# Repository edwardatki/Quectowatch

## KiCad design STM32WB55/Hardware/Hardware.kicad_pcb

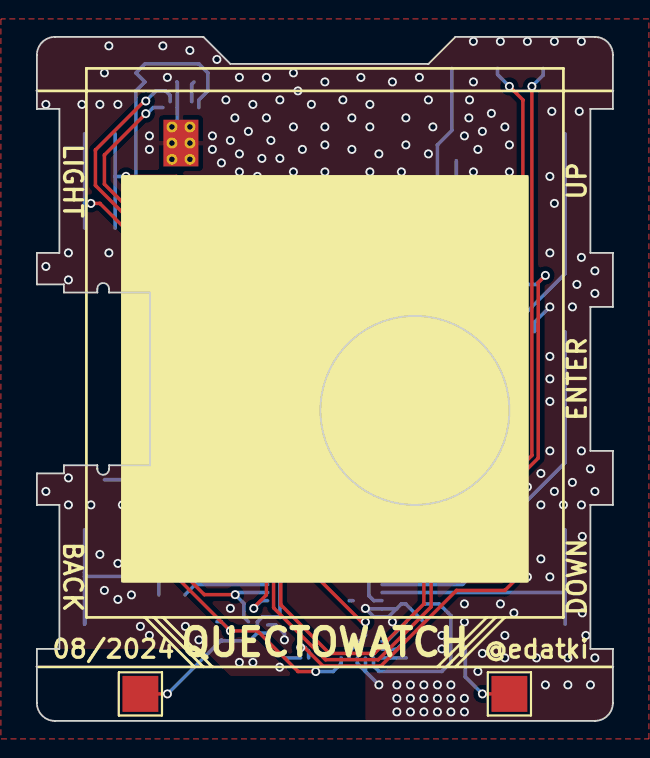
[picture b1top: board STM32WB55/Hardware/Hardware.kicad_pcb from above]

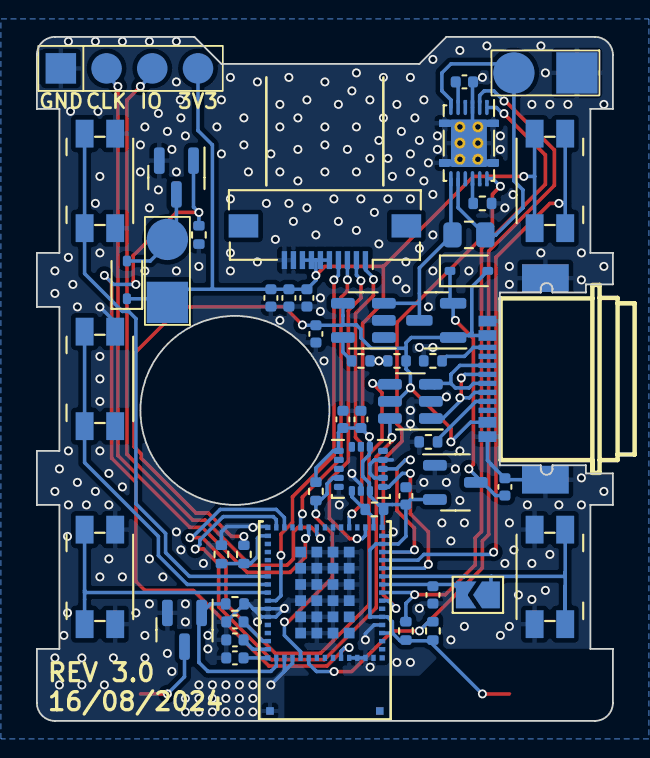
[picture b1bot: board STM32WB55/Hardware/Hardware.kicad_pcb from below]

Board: 2 copper layers, 32.0 x 38.0 mm, 51 parts (49 on the bottom side), 42 nets.

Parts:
C1, C7, C11: 100nF; C_0402_1005Metric
C2, C3, C4: 3.3pF; C_0402_1005Metric
C5: 470nF; C_0402_1005Metric
C6, C8, C9, C10, C13: 1uF; C_0402_1005Metric
C12: 10uF; C_0402_1005Metric
D1, D4: 1N5819WS; D_SOD-323
J1: USB_C_Receptacle_USB2.0; USB-C-SMD_SHOUHAN_TYPE-C-16PFS-2JCB1.2-H6.5
J2: PROG; 1x04_2.54_Pads
J3: BAT; 1x02_2.54_Pads
J4: LCD; Molex_54548-1071_1x10-1MP_P0.5mm_Horizontal
J5: AUX; 1x02_2.54_Pads
J6: LED+; TestPoint_Pad_2.0x2.0mm
J7: LED-; TestPoint_Pad_2.0x2.0mm
JP1: Jumper_2_Open; SolderJumper-2_P1.3mm_Open_TrianglePad1.0x1.5mm
Q1: AO3401A; SOT-23
Q2, Q3: AO3400A; SOT-23
R1, R2: 5K1; R_0402_1005Metric
R3: R01 1%; R_0805_2012Metric
R4: 470R; R_0402_1005Metric
R5: 1K; R_0402_1005Metric
R6, R7, R8, R10, R13, R14: 10K; R_0402_1005Metric
R9: 3.3K; R_0402_1005Metric
R12, R15: 100K; R_0402_1005Metric
SW1, SW2, SW3, SW4, SW5: SW_Push; Panasonic_EVQPUA_EVQPUJ
U1: USBLC6-2SC6; SOT-23-6
U2: STM32WB5MMGH6TR; LCC-LGA-86_L11.0-W7.3_STM32WB5MMGH6TR
U3: BQ27441DRZR-G1A; Texas_S-PDSO-N12
U4: TP4054; SOT-23-5
U5: LIS3DH; LGA-16_3x3mm_P0.5mm_LayoutBorder3x5y
U6: XC6206P332MR; SOT-23-3

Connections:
+3V3: C7.1, C8.1, C9.1, C11.1, C12.1, C13.1, D4.1 (K), J2.4, J4.5, J4.6, J4.7, J4.8, J5.1, J6.1, R7.1, R8.1, R13.1, R14.1, SW1.2, U2.4 (VREF+), U2.6 (VDDA), U2.15 (VBAT), U2.17 (VDDA), U5.1 (VDD_IO), U5.8 (CS), U5.14 (VDD), U6.2 (VO)
+BATT: Q1.3 (D), R3.2, U3.7 (SRN), U4.3 (BAT)
/AUX_EN: Q3.1 (G), R15.1, U2.56 (PA3)
/FG_INT: U2.8 (PC2), U3.12 (GPOUT)
/FG_SCL: R8.2, U2.52 (PA7), U3.2 (SCL)
/FG_SDA: R7.2, U2.9 (PC1), U3.1 (SDA)
/IMU_INT1: U2.14 (PB8), U5.11 (INT1)
/IMU_INT2: U2.12 (PC0), U5.9 (INT2)
/IMU_SCL: R14.2, U2.51 (PA9), U5.4 (SCL/SPC)
/IMU_SDA: R13.2, U2.18 (PB7), U5.6 (SDA/SDI/SDO)
/LCD_CS: J4.3, U2.27 (PA15)
/LCD_REFRESH: J4.4, U2.40 (PC13)
/LCD_SCLK: J4.1, U2.21 (PB3)
/LCD_SDI: J4.2, U2.19 (PB5)
/LIGHT_EN: Q2.1 (G), R12.1, U2.48 (PB2)
/SWDCLK: J2.2, U2.26 (PA14)
/SWDIO: J2.3, U2.25 (PA13)
/SW_LIGHT: SW1.1, U2.13 (PH3-BOOT0)
/USB_DN: U1.6 (I/O1), U2.30 (PA11)
/USB_DP: U1.4 (I/O2), U2.29 (PA12)
/~SW_DOWN: SW5.1, U2.39 (PB6)
/~SW_MENU: SW4.1, U2.38 (PB15)
/~SW_RESET: JP1.1 (A), SW2.1, U2.11 (PB9)
/~SW_UP: SW3.1, U2.37 (PB14)
GND: C1.2, C2.2, C3.2, C4.2, C5.2, C6.2, C7.2, C8.2, C9.2, C10.1, C11.2, C12.2, C13.2, J1.A1 (GND), J1.A12 (GND), J1.B1 (GND), J1.B12 (GND), J1.S1 (SHIELD), J2.1, J3.1, J4.9, J4.10, Q2.2 (S), Q3.2 (S), R1.2, R2.2, R5.1, R6.2, R9.1, R10.1, R12.2, R15.2, SW2.2, SW3.2, SW4.2, SW5.2, U1.2 (GND), U2.5 (VSS), U2.16 (VSS), U2.22 (PC10), U2.23 (PC11), U2.24 (PC12), U2.31 (VSS), U2.41 (PB12), U2.42 (PE4), U2.49 (PC4), U2.50 (PA8), U2.57 (VSS), U2.58 (ANT_IN), U2.59 (RF_OUT), U2.60 (VSS), U2.63 (PD14), U2.64 (PE1), U2.65 (PD13), U2.66 (PD12), U2.67 (PD7), U2.68 (PD2), U2.69 (PC9), U2.70 (PD3), U2.71 (PC7), U2.72 (PE3), U2.73 (PD4), U2.74 (PD9), U2.75 (PD8), U2.76 (PD15), U2.77 (PD10), U2.78 (PE2), U2.79 (PE0), U2.80 (PD5), U2.81 (PD6), U2.82 (PD11), U2.83 (PC8), U2.84 (VSS), U2.86 (VSS), U3.3 (V_{SS}), U3.13 (PAD), U4.2 (GND), U5.5 (GND), U5.7 (SDO/SA0), U5.10 (GND), U5.12 (GND), U6.1 (GND)
unnamed: J3.2, R3.1, U3.6 (BAT), U3.8 (SRP)
unnamed: R4.2, R5.2, U2.32 (VDDUSB)
unnamed: C10.2, D1.1 (K), Q1.2 (S), U6.3 (VI)
unnamed: D4.2 (A), J5.2, Q3.3 (D)
unnamed: J1.A5 (CC1), R2.1
unnamed: J1.B5 (CC2), R1.1
unnamed: J1.A6 (D+), J1.B6 (D+), U1.3 (I/O2)
unnamed: J1.A7 (D-), J1.B7 (D-), U1.1 (I/O1)
unnamed: J7.1, Q2.3 (D)
unnamed: C1.1, JP1.2 (B), U2.10 (NRST)
unnamed: C4.1, U2.47 (PB10)
unnamed: C3.1, U2.46 (PB11)
unnamed: C2.1, U2.45 (PC5)
unnamed: R6.1, U3.10 (BIN)
unnamed: C5.1, U3.5 (V_{DD})
unnamed: R9.2, U4.5 (PROG)
VBUS: C6.1, D1.2 (A), J1.A4 (VBUS), J1.A9 (VBUS), J1.B4 (VBUS), J1.B9 (VBUS), Q1.1 (G), R4.1, R10.2, U1.5 (VBUS), U4.4 (VCC)

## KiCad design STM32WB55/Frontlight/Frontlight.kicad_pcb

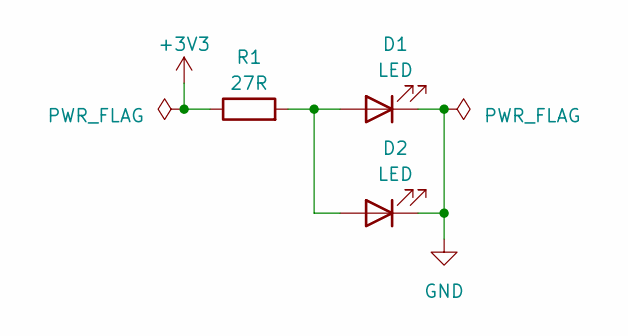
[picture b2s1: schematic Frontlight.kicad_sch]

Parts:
D1, D2: LED; LED_0603_1608Metric; LCSC C2290
R1: 27R; R_0603_1608Metric; LCSC C23140

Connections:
+3V3: R1.1
GND: D1.1 (K), D2.1 (K)
unnamed: D1.2 (A), D2.2 (A), R1.2

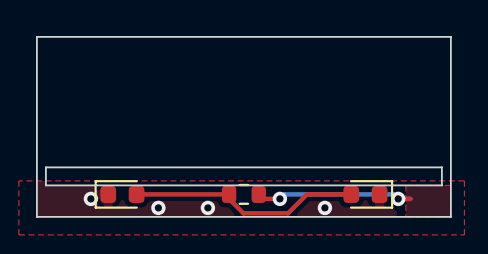
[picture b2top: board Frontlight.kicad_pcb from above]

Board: 2 copper layers, 23.0 x 10.0 mm, 3 parts (0 on the bottom side), 2 nets.

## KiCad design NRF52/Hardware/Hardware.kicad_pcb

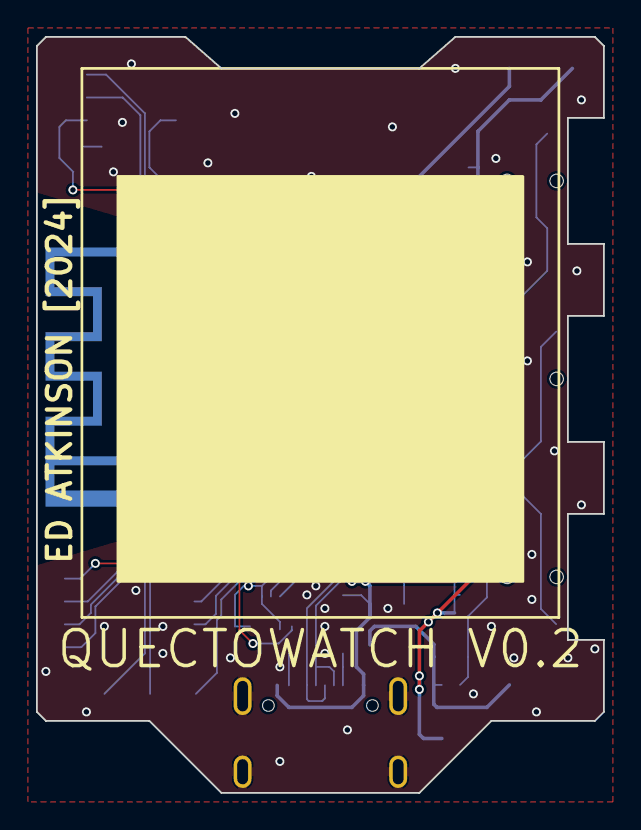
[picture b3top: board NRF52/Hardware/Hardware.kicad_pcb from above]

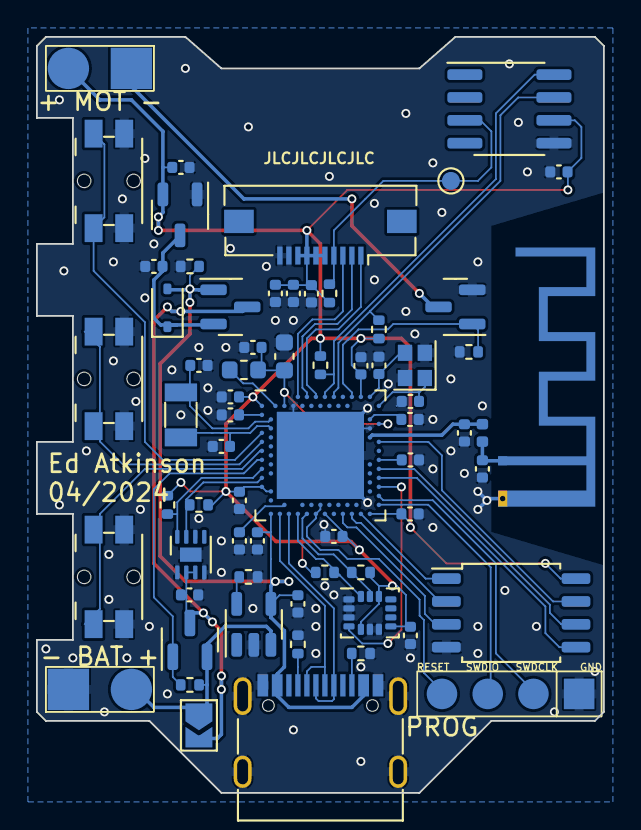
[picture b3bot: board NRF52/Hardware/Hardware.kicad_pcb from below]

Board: 2 copper layers, 31.5 x 42.0 mm, 66 parts (66 on the bottom side), 49 nets.

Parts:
AE1: Antenna_PCB; Texas_SWRA117D_2.4GHz_Left
C1, C12, C21, C22, C31, C34, C35, C36, C37: 1u; C_0402_1005Metric
C2, C3: 12p; C_0402_1005Metric
C4: 47n; C_0603_1608Metric
C5: 820p; C_0402_1005Metric
C6: 0p5; C_0402_1005Metric
C7, C20: 100p; C_0402_1005Metric
C8, C14, C15, C18, C19: 100n; C_0402_1005Metric
C9: 0p8; C_0402_1005Metric
C10, C11, C13: 4u7; C_0402_1005Metric
C16, C17: 6p8; C_0402_1005Metric
D1: 1N5819WS; D_SOD-323
J1: USB_C_Receptacle_USB2.0; USB_C_Receptacle_G-Switch_GT-USB-7010ASV
J2: LCD; Molex_54548-1071_1x10-1MP_P0.5mm_Horizontal
J3: PROG; Program_Pads
J4: BAT; Battery Pads
J5: MOTOR; Battery Pads
JP1: SolderJumper_2_Open; SolderJumper-2_P1.3mm_Open_TrianglePad1.0x1.5mm
L1: 4n7; L_0402_1005Metric
L3: 15u; L_0603_1608Metric
Q1, Q4: AO3401A; SOT-23
Q2: AO3400A; SOT-23
R1, R2: 5K1; R_0402_1005Metric
R3, R4, R6, R7, R8, R14, R15: 10K; R_0402_1005Metric
R5, R10, R11: 100K; R_0402_1005Metric
R9: 2K2; R_0402_1005Metric
SW1, SW2, SW3: SW_Push; Panasonic_EVQPUL_EVQPUC
TP2: LCD_REFRESH; TestPoint_Pad_D1.0mm
U1: nRF52840; Nordic_AQFN-73-1EP_7x7mm_P0.5mm
U2: TP4054; SOT-23-5
U3: MAX17048; TDFN-8-1EP_2x2mm_P0.5mm_EP0.8x1.2mm
U4: XC6206PxxxMR; SOT-23-3
U5: LSM6DS3; LGA-14_3x2.5mm_P0.5mm_LayoutBorder3x4y
U6: DS3231MZ; SOIC-8_3.9x4.9mm_P1.27mm
U7: W25Q128JVS; SOIC-8_5.23x5.23mm_P1.27mm
Y1: 32MHz 8pF ±10ppm; Crystal_SMD_2016-4Pin_2.0x1.6mm
Y2: 32.768kHz 6pF ±20ppm; Crystal_SMD_3215-2Pin_3.2x1.5mm

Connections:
+3V3: C12.1, C13.1, C14.1, C15.1, C18.1, C20.1, C21.1, C22.1, C35.1, C36.1, C37.1, J2.5, J2.6, J2.7, J2.8, J5.2, R4.1, R5.1, R6.1, R7.1, R8.1, R14.1, R15.1, U1.A22 (VDD), U1.AD14 (VDD), U1.AD23 (VDD), U1.B1 (VDD), U1.W1 (VDD), U1.Y2 (VDDH), U4.2 (VO), U5.5 (VDDIO), U5.8 (VDD), U5.12 (CS), U6.6 (VBAT), U7.8 (VCC)
+BATT: C19.1, JP1.2 (B), Q1.3 (D), Q4.3 (D), U3.2 (CELL), U3.3 (VDD)
/DOWN_BUTTON: SW3.1, U1.L1 (P0.06)
/FG_SCL: R8.2, U1.U1 (TRACEDATA1/P0.12), U3.7 (SCL)
/FG_SDA: R7.2, U1.R1 (TRACEDATA3/P1.09), U3.8 (SDA)
/IMU_INT: U1.W24 (P1.02), U5.4 (INT1)
/IMU_SCL: R6.2, U1.AD10 (P0.15), U5.13 (SCL)
/IMU_SDA: R4.2, U1.AD8 (P0.13), U5.14 (SDA)
/LCD_CS: J2.3, U1.A8 (AIN7/P0.31)
/LCD_REFRESH: J2.4, R5.2, TP2.1, U6.3 (~INT/SQW)
/LCD_SCLK: J2.1, U1.A12 (AIN0/P0.02)
/LCD_SDI: J2.2, U1.A10 (AIN5/P0.29)
/MENU_BUTTON: SW1.1, U1.J1 (AIN2/P0.04)
/MOTOR_EN: Q2.1 (G), R11.1, U1.A20 (P1.10)
/POWER_LATCH: Q4.1 (G), R10.1, U1.N1 (P0.08)
/QSPI_CS: U1.AD22 (TRACEDATA0/P1.00), U7.1 (~CS)
/QSPI_D0: U1.U24 (P1.04), U7.5 (DI(IO0))
/QSPI_D1: U1.AD20 (P0.24), U7.2 (DO(IO1))
/QSPI_D2: U1.AD18 (P0.22), U7.3 (IO2)
/QSPI_D3: U1.J24 (NFC2/P0.10), U7.7 (IO3)
/QSPI_SCK: U1.R24 (P1.06), U7.6 (CLK)
/RTC_SCL: R15.2, U1.A16 (P1.13), U6.7 (SDA)
/RTC_SDA: R14.2, U1.A14 (P1.15), U6.8 (SCL)
/SWDCLK: J3.2, U1.AA24 (SWDCLK)
/SWDIO: J3.3, U1.AC24 (SWDIO)
/UP_BUTTON: SW2.1, U1.G1 (P0.26)
/USB_DN: J1.A7 (D-), J1.B7 (D-), U1.AD4 (D-)
/USB_DP: J1.A6 (D+), J1.B6 (D+), U1.AD6 (D+)
/~RESET: J3.4, U1.AC13 (P0.18/~RESET), U1.AD12 (P0.17)
GND: AE1.2 (PCB_Trace), C1.2, C2.1, C3.2, C4.2, C5.2, C6.2, C7.2, C8.2, C9.2, C10.2, C11.2, C12.2, C13.2, C14.2, C15.2, C16.1, C17.2, C18.2, C19.2, C20.2, C21.2, C22.2, C31.2, C34.1, C35.2, C36.2, C37.2, J1.A1 (GND), J1.A12 (GND), J1.B1 (GND), J1.B12 (GND), J1.S1 (SHIELD), J2.9, J2.10, J3.1, J4.1, Q2.2 (S), R1.2, R2.2, R3.1, R9.1, R11.2, SW1.2, SW2.2, SW3.2, U1.B7 (VSS), U1.EP (VSS), U1.F23 (VSS_PA), U2.2 (GND), U3.1 (CTG), U3.4 (GND), U3.6 (QSTRT), U3.9 (GND), U4.1 (GND), U5.1 (SDO/SA0), U5.2 (SDX), U5.3 (SCX), U5.6 (GND), U5.7 (GND), U6.5 (GND), U7.4 (GND), Y1.2, Y1.4
unnamed: C34.2, D1.1 (K), Q1.2 (S), U4.3 (VI)
unnamed: J4.2, JP1.1 (A), Q4.2 (S), R10.2, U2.3 (BAT)
unnamed: AE1.1 (FEED), C6.1, L1.1
unnamed: J1.A5 (CC1), R2.1
unnamed: J1.B5 (CC2), R1.1
unnamed: J5.1, Q2.3 (D)
unnamed: C9.1, L1.2, U1.H23 (ANT)
unnamed: L3.2, U1.B3 (DCC)
unnamed: C8.1, U1.C1 (DEC1)
unnamed: C7.1, U1.D23 (DEC3)
unnamed: C1.1, C4.1, L3.1, U1.B5 (DEC4), U1.E24 (DEC6)
unnamed: C5.1, U1.N24 (DEC5)
unnamed: C10.1, U1.AC5 (DECUSB)
unnamed: C2.2, U1.B24 (XC1), Y1.1
unnamed: C3.1, U1.A23 (XC2), Y1.3
unnamed: C16.2, U1.D2 (XL1/P0.00), Y2.2
unnamed: C17.1, U1.F2 (XL2/P0.01), Y2.1
unnamed: R9.2, U2.5 (PROG)
VBUS: C11.1, C31.1, D1.2 (A), J1.A4 (VBUS), J1.A9 (VBUS), J1.B4 (VBUS), J1.B9 (VBUS), Q1.1 (G), R3.2, U1.AD2 (VBUS), U2.4 (VCC)

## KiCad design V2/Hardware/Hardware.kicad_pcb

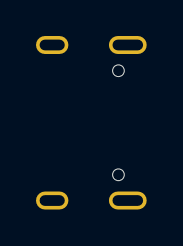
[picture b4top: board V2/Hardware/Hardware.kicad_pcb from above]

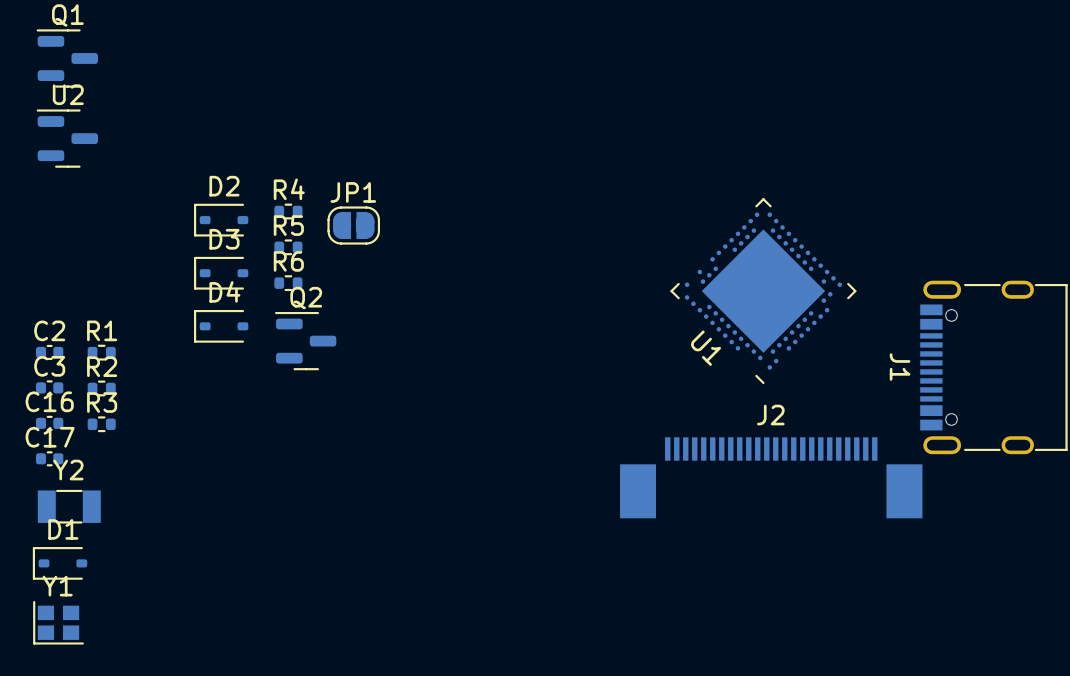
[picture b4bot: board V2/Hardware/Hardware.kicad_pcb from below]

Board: 2 copper layers, 23 parts (22 on the bottom side), 26 nets, no tracks yet.

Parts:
C2, C3: 12p; C_0402_1005Metric
C16, C17: 6p8; C_0402_1005Metric
D1, D2, D3, D4: 1N5819WS; D_SOD-323
J1: USB_C_Receptacle_USB2.0; USB_C_Receptacle_G-Switch_GT-USB-7010ASV
J2: 1.54 E-INK; 1.54_Epaper_Display
JP1: Jumper_2_Open; SolderJumper-2_P1.3mm_Open_RoundedPad1.0x1.5mm
Q1: AO3401A; SOT-23
Q2: AO3400A; SOT-23
R1, R2: 5K1; R_0402_1005Metric
R3, R4: 100K; R_0402_1005Metric
R5: 10K; R_0402_1005Metric
R6: 0R47; R_0402_1005Metric
U1: nRF52840; Nordic_AQFN-73-1EP_7x7mm_P0.5mm
U2: MCP1700x-180xxTT; SOT-23
Y1: 32MHz 8pF ±10ppm; Crystal_SMD_2016-4Pin_2.0x1.6mm
Y2: 32.768kHz 6pF ±20ppm; Crystal_SMD_3215-2Pin_3.2x1.5mm

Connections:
+1V8: J2.15, J2.16, R4.2, U1.A22 (VDD), U1.AD14 (VDD), U1.AD23 (VDD), U1.B1 (VDD), U1.W1 (VDD), U1.Y2 (VDDH), U2.2 (VO)
/EINK_BUSY: J2.9, U1.H2 (P0.27)
/EINK_CS: J2.12, U1.B9 (AIN6/P0.30)
/EINK_DC: J2.11, U1.B11 (AIN4/P0.28)
/EINK_RES: J2.10, U1.G1 (P0.26)
/EINK_SCLK: J2.13, U1.A8 (AIN7/P0.31)
/EINK_SDI: J2.14, U1.A10 (AIN5/P0.29)
/GDR: J2.2, Q2.1 (G), R5.2
/PREVGH: D4.1 (K), J2.21
/PREVGL: D2.2 (A), J2.23
/RESE: J2.3, Q2.2 (S), R6.2
/USB_DN: J1.A7 (D-), J1.B7 (D-), U1.AD4 (D-)
/USB_DP: J1.A6 (D+), J1.B6 (D+), U1.AD6 (D+)
/~RESET: JP1.2 (B), R4.1, U1.AC13 (P0.18/~RESET)
GND: C2.1, C3.2, C16.1, C17.2, D3.1 (K), J1.A1 (GND), J1.A12 (GND), J1.B1 (GND), J1.B12 (GND), J1.S1 (SHIELD), J2.8, J2.17, JP1.1 (A), R1.2, R2.2, R3.1, R5.1, R6.1, U1.B7 (VSS), U1.EP (VSS), U1.F23 (VSS_PA), U2.1 (GND), Y1.2, Y1.4
unnamed: D1.1 (K), Q1.2 (S), U2.3 (VI)
unnamed: D2.1 (K), D3.2 (A)
unnamed: D4.2 (A), Q2.3 (D)
unnamed: J1.A5 (CC1), R2.1
unnamed: J1.B5 (CC2), R1.1
unnamed: U1.B5 (DEC4), U1.E24 (DEC6)
unnamed: C2.2, U1.B24 (XC1), Y1.1
unnamed: C3.1, U1.A23 (XC2), Y1.3
unnamed: C16.2, U1.D2 (XL1/P0.00), Y2.2
unnamed: C17.1, U1.F2 (XL2/P0.01), Y2.1
VBUS: D1.2 (A), J1.A4 (VBUS), J1.A9 (VBUS), J1.B4 (VBUS), J1.B9 (VBUS), Q1.1 (G), R3.2, U1.AD2 (VBUS)

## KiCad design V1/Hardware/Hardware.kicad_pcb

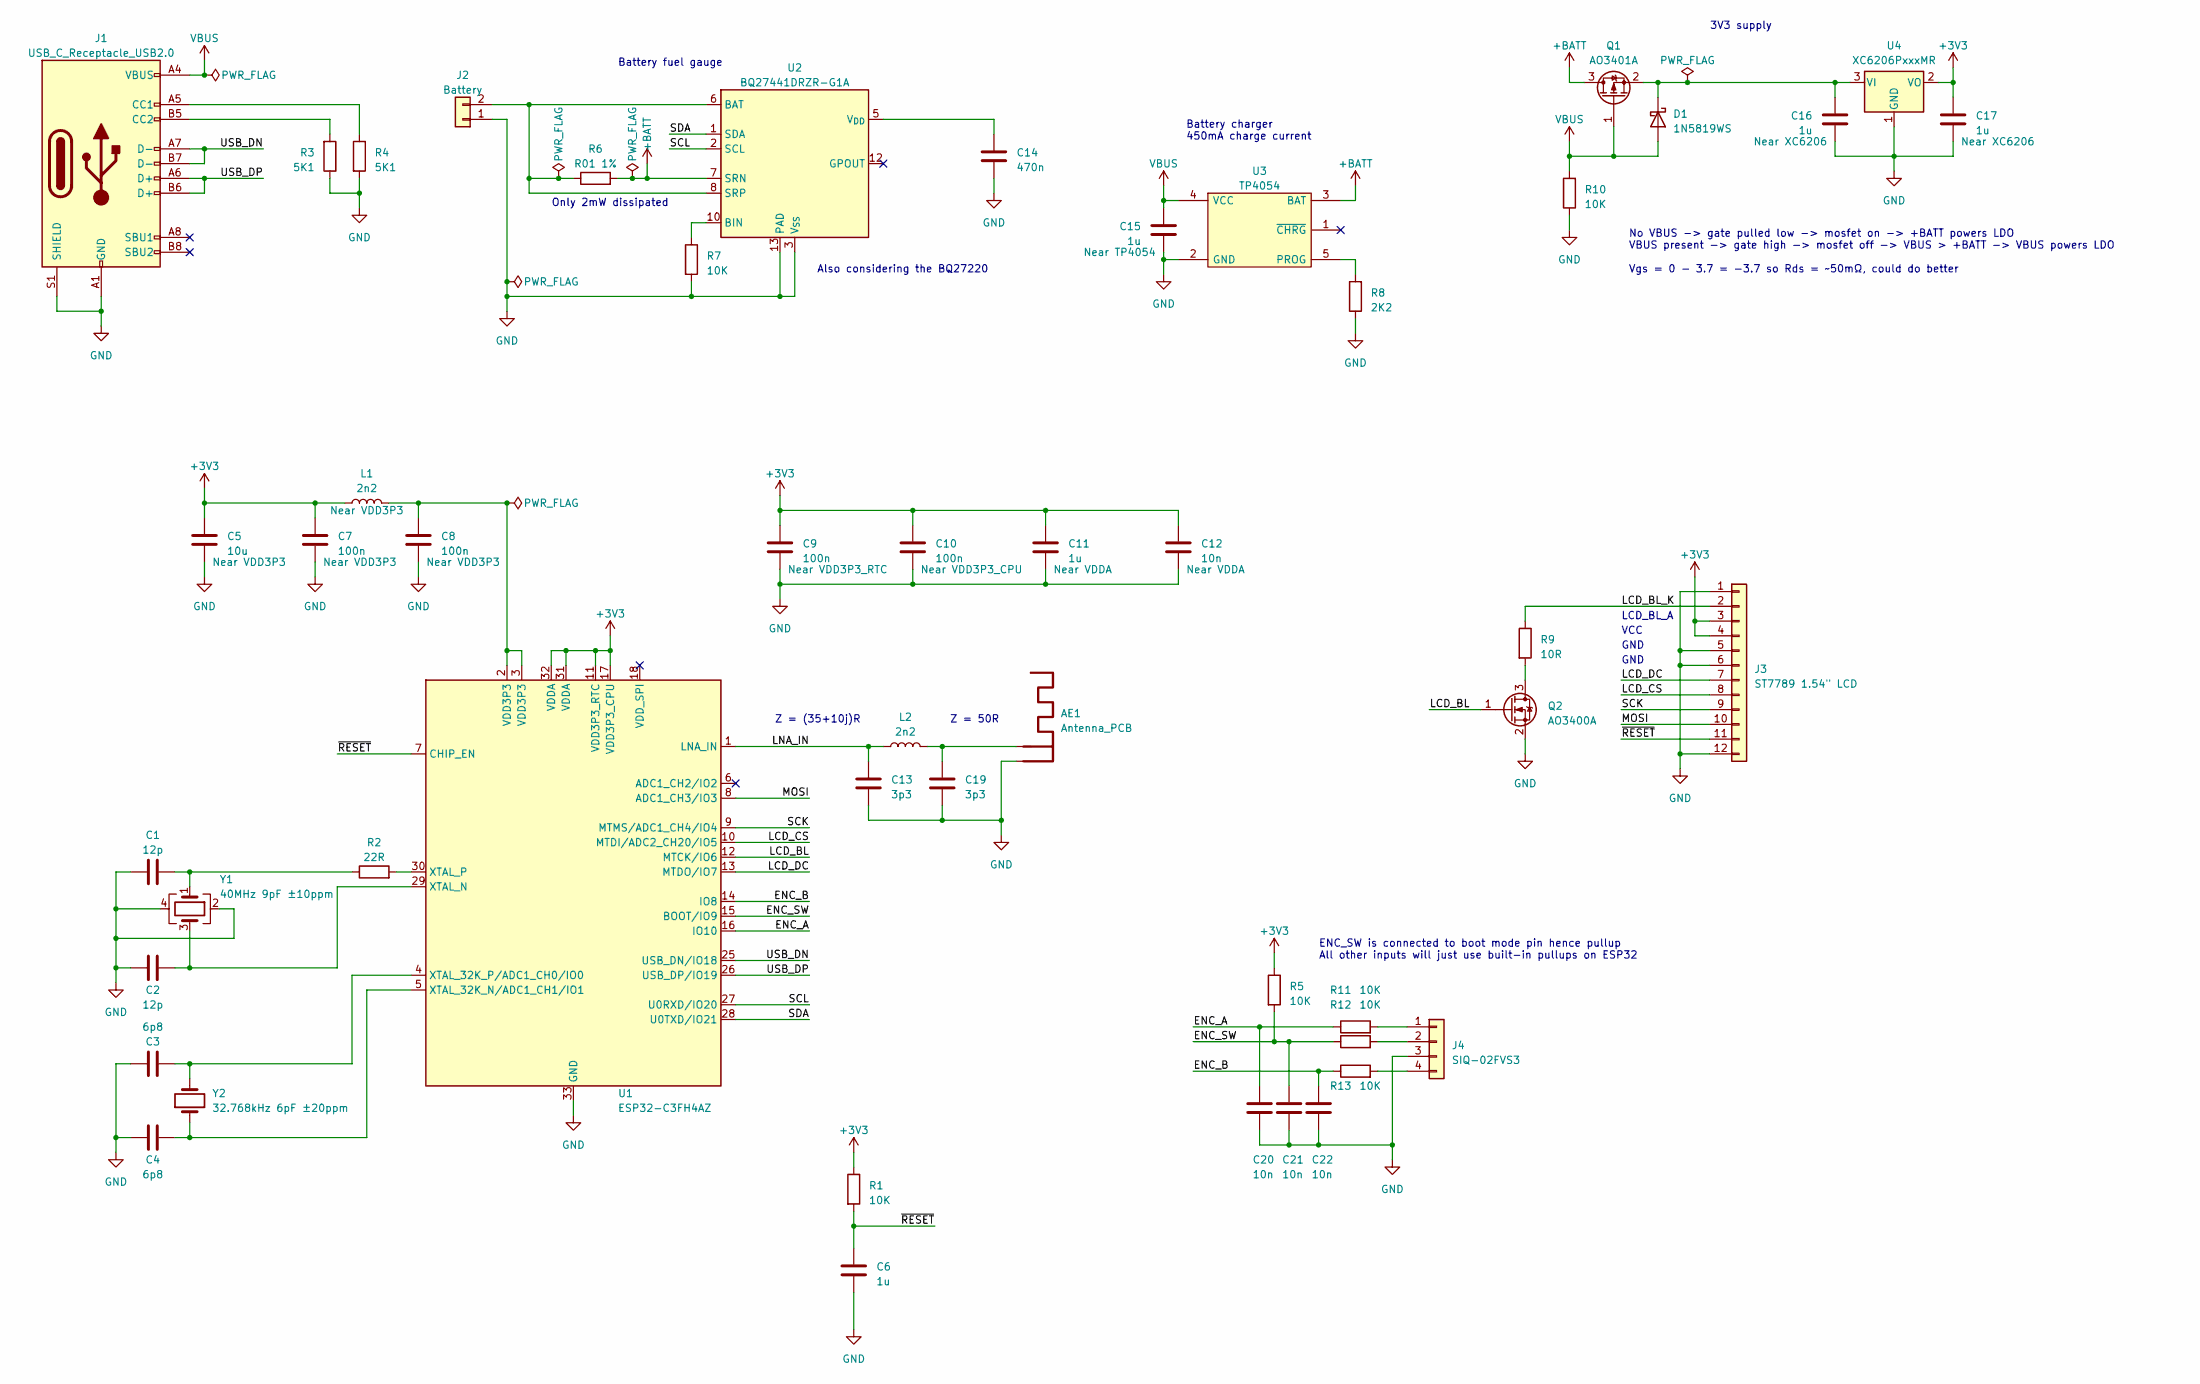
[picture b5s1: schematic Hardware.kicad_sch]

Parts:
AE1: Antenna_PCB; Texas_SWRA117D_2.4GHz_Left
C1, C2: 12p; C_0402_1005Metric; LCSC C1547
C3, C4: 6p8; C_0402_1005Metric; LCSC C1576
C5: 10u; C_0402_1005Metric; LCSC C15525
C6, C11, C15, C16, C17: 1u; C_0402_1005Metric; LCSC C52923
C7, C8, C9, C10: 100n; C_0402_1005Metric; LCSC C1525
C12, C20, C21, C22: 10n; C_0402_1005Metric; LCSC C15195
C13, C19: 3p3; C_0402_1005Metric; LCSC C1565
C14: 470n; C_0402_1005Metric; LCSC C47339
D1: 1N5819WS; D_SOD-323; LCSC C191023
J1: USB_C_Receptacle_USB2.0; USB_C_Receptacle_G-Switch_GT-USB-7010ASV; LCSC C2765186
J2: Battery; JST_PH_S2B-PH-SM4-TB_1x02-1MP_P2.00mm_Horizontal; LCSC C295747
J3: ST7789 1.54" LCD; 1.54 ST7789
J4: SIQ-02FVS3; LCSC C2925423
L1, L2: 2n2; L_0402_1005Metric; LCSC C86061
Q1: AO3401A; SOT-23; LCSC C15127
Q2: AO3400A; SOT-23; LCSC C20917
R1, R5, R7, R10, R11, R12, R13: 10K; R_0402_1005Metric; LCSC C25744
R2: 22R; R_0402_1005Metric; LCSC C25092
R3, R4: 5K1; R_0402_1005Metric; LCSC C25905
R6: R01 1%; R_0805_2012Metric; LCSC C3024467
R8: 2K2; R_0402_1005Metric; LCSC C25879
R9: 10R; R_0402_1005Metric; LCSC C25077
U1: ESP32-C3FH4AZ; QFN-32-1EP_5x5mm_P0.5mm_EP3.6x3.6mm_ThermalVias; LCSC C2858491
U2: BQ27441DRZR-G1A; Texas_S-PDSO-N12; LCSC C473397
U3: TP4054; SOT-23-5; Manufacturer_Part_Number TP4054-42-SOT25-R; LCSC C32574
U4: XC6206PxxxMR; SOT-23-3; LCSC C5446
Y1: 40MHz 9pF ±10ppm; Crystal_SMD_2520-4Pin_2.5x2.0mm; LCSC C557159
Y2: 32.768kHz 6pF ±20ppm; Crystal_SMD_3215-2Pin_3.2x1.5mm; LCSC C32346

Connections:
+3V3: C5.1, C7.1, C9.1, C10.1, C11.1, C12.1, C17.1, J3.3, J3.4, L1.1, R1.1, R5.1, U1.11 (VDD3P3_RTC), U1.17 (VDD3P3_CPU), U1.31 (VDDA), U1.32 (VDDA), U4.2 (VO)
+BATT: Q1.3 (D), R6.2, U2.7 (SRN), U3.3 (BAT)
/ENC_A: C20.1, R11.1, U1.16 (IO10)
/ENC_B: C22.1, R13.1, U1.14 (IO8)
/ENC_SW: C21.1, R5.2, R12.1, U1.15 (BOOT/IO9)
/LCD_BL: Q2.1 (G), U1.12 (MTCK/IO6)
/LCD_BL_K: J3.2, R9.1
/LCD_CS: J3.8, U1.10 (MTDI/ADC2_CH20/IO5)
/LCD_DC: J3.7, U1.13 (MTDO/IO7)
/LNA_IN: C13.1, L2.1, U1.1 (LNA_IN)
/MOSI: J3.10, U1.8 (ADC1_CH3/IO3)
/SCK: J3.9, U1.9 (MTMS/ADC1_CH4/IO4)
/SCL: U1.27 (U0RXD/IO20), U2.2 (SCL)
/SDA: U1.28 (U0TXD/IO21), U2.1 (SDA)
/USB_DN: J1.A7 (D-), J1.B7 (D-), U1.25 (USB_DN/IO18)
/USB_DP: J1.A6 (D+), J1.B6 (D+), U1.26 (USB_DP/IO19)
/~RESET: C6.1, J3.11, R1.2, U1.7 (CHIP_EN)
GND: AE1.2 (PCB_Trace), C1.1, C2.2, C3.1, C4.2, C5.2, C6.2, C7.2, C8.2, C9.2, C10.2, C11.2, C12.2, C13.2, C14.2, C15.2, C16.2, C17.2, C19.2, C20.2, C21.2, C22.2, J1.A1 (GND), J1.A12 (GND), J1.B1 (GND), J1.B12 (GND), J1.S1 (SHIELD), J2.1, J3.1, J3.5, J3.6, J3.12, J4.3, Q2.2 (S), R3.1, R4.2, R7.2, R8.1, R10.1, U1.33 (GND), U2.3 (V_{SS}), U2.13 (PAD), U3.2 (GND), U4.1 (GND), Y1.2, Y1.4
unnamed: AE1.1 (FEED), C19.1, L2.2
unnamed: C1.2, R2.1, Y1.1
unnamed: C8.1, L1.2, U1.2 (VDD3P3), U1.3 (VDD3P3)
unnamed: C16.1, D1.1 (K), Q1.2 (S), U4.3 (VI)
unnamed: J1.A5 (CC1), R4.1
unnamed: J1.B5 (CC2), R3.2
unnamed: J2.2, R6.1, U2.6 (BAT), U2.8 (SRP)
unnamed: J4.1, R11.2
unnamed: J4.2, R12.2
unnamed: J4.4, R13.2
unnamed: Q2.3 (D), R9.2
unnamed: C4.1, U1.5 (XTAL_32K_N/ADC1_CH1/IO1), Y2.1
unnamed: C3.2, U1.4 (XTAL_32K_P/ADC1_CH0/IO0), Y2.2
unnamed: C2.1, U1.29 (XTAL_N), Y1.3
unnamed: R2.2, U1.30 (XTAL_P)
unnamed: R7.1, U2.10 (BIN)
unnamed: C14.1, U2.5 (V_{DD})
unnamed: R8.2, U3.5 (PROG)
VBUS: C15.1, D1.2 (A), J1.A4 (VBUS), J1.A9 (VBUS), J1.B4 (VBUS), J1.B9 (VBUS), Q1.1 (G), R10.2, U3.4 (VCC)

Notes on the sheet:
No VBUS -> gate pulled low -> mosfet on -> +BATT powers LDO VBUS present -> gate high -> mosfet off -> VBUS > +BATT -> VBUS powers LDO Vgs = 0 - 3.7 = -3.7 so Rds = ~50mΩ, could do better
Battery fuel gauge
Z = (35+10j)R
GND
LCD_BL_A
3V3 supply
Only 2mW dissipated
Also considering the BQ27220
Battery charger 450mA charge current
ENC_SW is connected to boot mode pin hence pullup All other inputs will just use built-in pullups on ESP32
VCC
Z = 50R

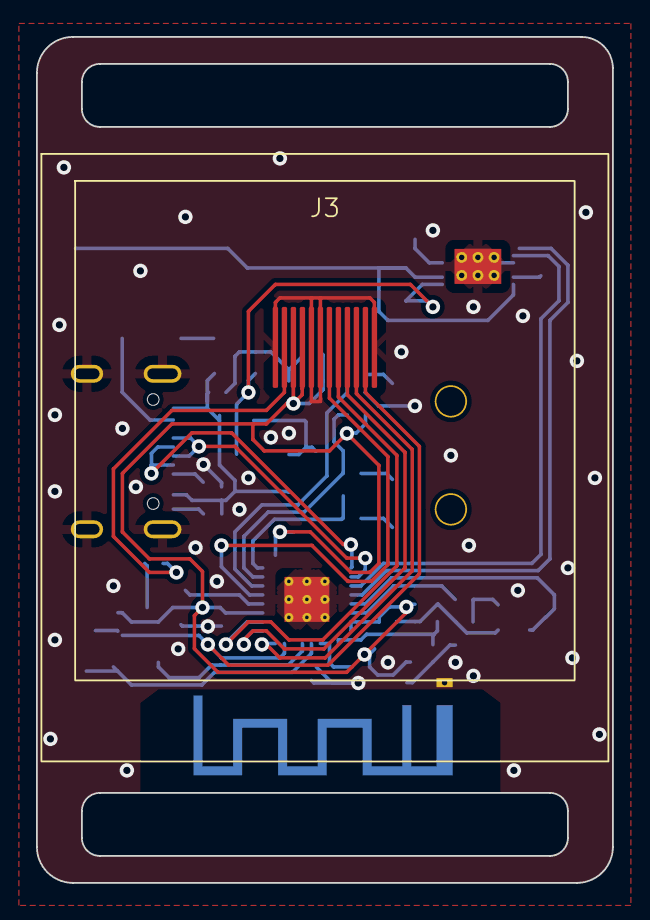
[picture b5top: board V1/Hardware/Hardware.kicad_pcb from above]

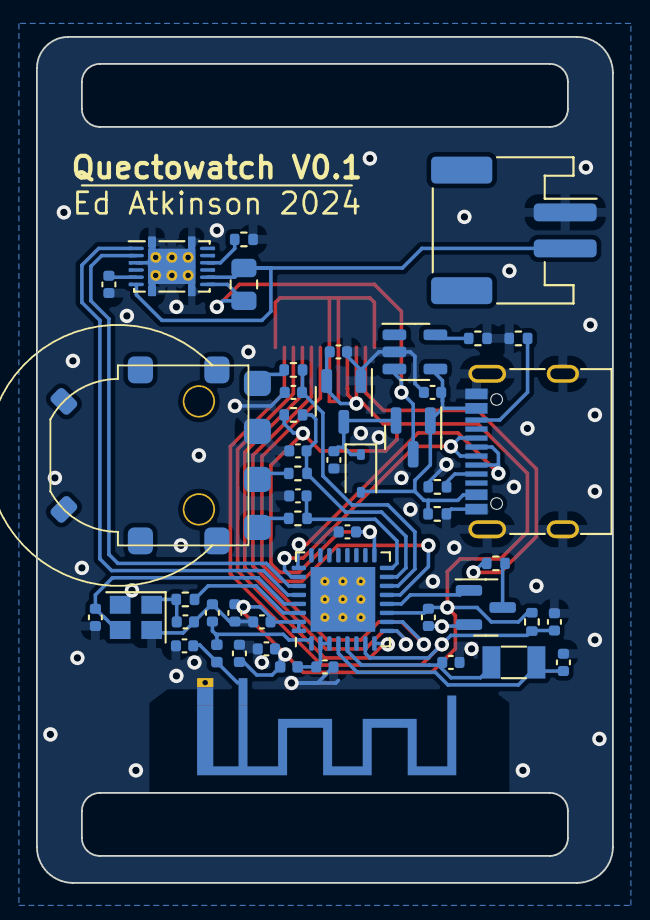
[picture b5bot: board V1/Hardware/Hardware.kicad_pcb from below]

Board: 2 copper layers, 32.0 x 47.0 mm, 50 parts (49 on the bottom side), 37 nets.

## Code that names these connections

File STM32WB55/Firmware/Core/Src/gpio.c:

/* USER CODE BEGIN Header */
/**
  ******************************************************************************
  * @file    gpio.c
  * @brief   This file provides code for the configuration
  *          of all used GPIO pins.
  ******************************************************************************
  * @attention
  *
  * Copyright (c) 2024 STMicroelectronics.
  * All rights reserved.
  *
  * This software is licensed under terms that can be found in the LICENSE file
  * in the root directory of this software component.
  * If no LICENSE file comes with this software, it is provided AS-IS.
  *
  ******************************************************************************
  */
/* USER CODE END Header */

/* Includes ------------------------------------------------------------------*/
#include "gpio.h"

/* USER CODE BEGIN 0 */

/* USER CODE END 0 */

/*----------------------------------------------------------------------------*/
/* Configure GPIO                                                             */
/*----------------------------------------------------------------------------*/
/* USER CODE BEGIN 1 */

/* USER CODE END 1 */

/** Configure pins as
        * Analog
        * Input
        * Output
        * EVENT_OUT
        * EXTI
        * Free pins are configured automatically as Analog (this feature is enabled through
        * the Code Generation settings)
*/
void MX_GPIO_Init(void)
{

  GPIO_InitTypeDef GPIO_InitStruct = {0};

  /* GPIO Ports Clock Enable */
  __HAL_RCC_GPIOA_CLK_ENABLE();
  __HAL_RCC_GPIOC_CLK_ENABLE();
  __HAL_RCC_GPIOD_CLK_ENABLE();
  __HAL_RCC_GPIOB_CLK_ENABLE();
  __HAL_RCC_GPIOE_CLK_ENABLE();
  __HAL_RCC_GPIOH_CLK_ENABLE();

  /*Configure GPIO pin Output Level */
  HAL_GPIO_WritePin(GPIOA, LCD_CS_Pin|AUX_EN_Pin, GPIO_PIN_RESET);

  /*Configure GPIO pin Output Level */
  HAL_GPIO_WritePin(LCD_REFRESH_GPIO_Port, LCD_REFRESH_Pin, GPIO_PIN_RESET);

  /*Configure GPIO pins : PAPin PAPin */
  GPIO_InitStruct.Pin = LCD_CS_Pin|AUX_EN_Pin;
  GPIO_InitStruct.Mode = GPIO_MODE_OUTPUT_PP;
  GPIO_InitStruct.Pull = GPIO_NOPULL;
  GPIO_InitStruct.Speed = GPIO_SPEED_FREQ_LOW;
  HAL_GPIO_Init(GPIOA, &GPIO_InitStruct);

  /*Configure GPIO pins : PC10 PC9 PC11 PC12
                           PC6 PC7 PC8 PC4
                           PC3 PC5 */
  GPIO_InitStruct.Pin = GPIO_PIN_10|GPIO_PIN_9|GPIO_PIN_11|GPIO_PIN_12
                          |GPIO_PIN_6|GPIO_PIN_7|GPIO_PIN_8|GPIO_PIN_4
                          |GPIO_PIN_3|GPIO_PIN_5;
  GPIO_InitStruct.Mode = GPIO_MODE_ANALOG;
  GPIO_InitStruct.Pull = GPIO_NOPULL;
  HAL_GPIO_Init(GPIOC, &GPIO_InitStruct);

  /*Configure GPIO pins : PD2 PD7 PD5 PD12
                           PD3 PD1 PD0 PD6
                           PD13 PD4 PD8 PD9
                           PD14 PD10 PD11 PD15 */
  GPIO_InitStruct.Pin = GPIO_PIN_2|GPIO_PIN_7|GPIO_PIN_5|GPIO_PIN_12
                          |GPIO_PIN_3|GPIO_PIN_1|GPIO_PIN_0|GPIO_PIN_6
                          |GPIO_PIN_13|GPIO_PIN_4|GPIO_PIN_8|GPIO_PIN_9
                          |GPIO_PIN_14|GPIO_PIN_10|GPIO_PIN_11|GPIO_PIN_15;
  GPIO_InitStruct.Mode = GPIO_MODE_ANALOG;
  GPIO_InitStruct.Pull = GPIO_NOPULL;
  HAL_GPIO_Init(GPIOD, &GPIO_InitStruct);

  /*Configure GPIO pins : PA10 PA2 PA1 PA0
                           PA6 PA8 PA5 PA4 */
  GPIO_InitStruct.Pin = GPIO_PIN_10|GPIO_PIN_2|GPIO_PIN_1|GPIO_PIN_0
                          |GPIO_PIN_6|GPIO_PIN_8|GPIO_PIN_5|GPIO_PIN_4;
  GPIO_InitStruct.Mode = GPIO_MODE_ANALOG;
  GPIO_InitStruct.Pull = GPIO_NOPULL;
  HAL_GPIO_Init(GPIOA, &GPIO_InitStruct);

  /*Configure GPIO pins : PE1 PE0 PE2 PE4
                           PE3 */
  GPIO_InitStruct.Pin = GPIO_PIN_1|GPIO_PIN_0|GPIO_PIN_2|GPIO_PIN_4
                          |GPIO_PIN_3;
  GPIO_InitStruct.Mode = GPIO_MODE_ANALOG;
  GPIO_InitStruct.Pull = GPIO_NOPULL;
  HAL_GPIO_Init(GPIOE, &GPIO_InitStruct);

  /*Configure GPIO pins : PB13 PB4 PB12 PB1
                           PB0 PB11 PB10 */
  GPIO_InitStruct.Pin = GPIO_PIN_13|GPIO_PIN_4|GPIO_PIN_12|GPIO_PIN_1
                          |GPIO_PIN_0|GPIO_PIN_11|GPIO_PIN_10;
  GPIO_InitStruct.Mode = GPIO_MODE_ANALOG;
  GPIO_InitStruct.Pull = GPIO_NOPULL;
  HAL_GPIO_Init(GPIOB, &GPIO_InitStruct);

  /*Configure GPIO pins : PBPin PBPin PBPin */
  GPIO_InitStruct.Pin = SW_UP_Pin|SW_MENU_Pin|SW_DOWN_Pin;
  GPIO_InitStruct.Mode = GPIO_MODE_IT_FALLING;
  GPIO_InitStruct.Pull = GPIO_PULLUP;
  HAL_GPIO_Init(GPIOB, &GPIO_InitStruct);

  /*Configure GPIO pin : PtPin */
  GPIO_InitStruct.Pin = SW_LIGHT_Pin;
  GPIO_InitStruct.Mode = GPIO_MODE_IT_RISING_FALLING;
  GPIO_InitStruct.Pull = GPIO_NOPULL;
  HAL_GPIO_Init(SW_LIGHT_GPIO_Port, &GPIO_InitStruct);

  /*Configure GPIO pins : PH1 PH0 */
  GPIO_InitStruct.Pin = GPIO_PIN_1|GPIO_PIN_0;
  GPIO_InitStruct.Mode = GPIO_MODE_ANALOG;
  GPIO_InitStruct.Pull = GPIO_NOPULL;
  HAL_GPIO_Init(GPIOH, &GPIO_InitStruct);

  /*Configure GPIO pins : PBPin PBPin */
  GPIO_InitStruct.Pin = IMU_INT1_Pin|SW_RESET_Pin;
  GPIO_InitStruct.Mode = GPIO_MODE_INPUT;
  GPIO_InitStruct.Pull = GPIO_NOPULL;
  HAL_GPIO_Init(GPIOB, &GPIO_InitStruct);

  /*Configure GPIO pins : PCPin PCPin */
  GPIO_InitStruct.Pin = IMU_INT2_Pin|FG_INT_Pin;
  GPIO_InitStruct.Mode = GPIO_MODE_INPUT;
  GPIO_InitStruct.Pull = GPIO_NOPULL;
  HAL_GPIO_Init(GPIOC, &GPIO_InitStruct);

  /*Configure GPIO pin : PtPin */
  GPIO_InitStruct.Pin = LCD_REFRESH_Pin;
  GPIO_InitStruct.Mode = GPIO_MODE_OUTPUT_PP;
  GPIO_InitStruct.Pull = GPIO_PULLUP;
  GPIO_InitStruct.Speed = GPIO_SPEED_FREQ_LOW;
  HAL_GPIO_Init(LCD_REFRESH_GPIO_Port, &GPIO_InitStruct);

  /* EXTI interrupt init*/
  HAL_NVIC_SetPriority(EXTI3_IRQn, 0, 0);
  HAL_NVIC_EnableIRQ(EXTI3_IRQn);

  HAL_NVIC_SetPriority(EXTI9_5_IRQn, 0, 0);
  HAL_NVIC_EnableIRQ(EXTI9_5_IRQn);

  HAL_NVIC_SetPriority(EXTI15_10_IRQn, 0, 0);
  HAL_NVIC_EnableIRQ(EXTI15_10_IRQn);

}

/* USER CODE BEGIN 2 */

/* USER CODE END 2 */

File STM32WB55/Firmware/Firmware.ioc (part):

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Mcu.Name=STM32WB55VGYx
Mcu.Package=WLCSP100
Mcu.UserName=STM32WB55VGYx
PA11.Mode=Device
PA11.Signal=USB_DM
PA12.Mode=Device
PA12.Signal=USB_DP
PA13.Mode=Serial_Wire
PA13.Signal=SYS_JTMS-SWDIO
PA14.Mode=Serial_Wire
PA14.Signal=SYS_JTCK-SWCLK
PA15.GPIOParameters=GPIO_Label
PA15.GPIO_Label=LCD_CS
PA15.Signal=GPIO_Output
PA3.GPIOParameters=GPIO_Label
PA3.GPIO_Label=AUX_EN
PA3.Signal=GPIO_Output
PA7.GPIOParameters=GPIO_Label
PA7.GPIO_Label=FG_SCL
PA7.Mode=I2C
PA7.Signal=I2C3_SCL
PA9.GPIOParameters=GPIO_Label
PA9.GPIO_Label=IMU_SCL
PA9.Mode=I2C
PA9.Signal=I2C1_SCL
PB14.GPIOParameters=GPIO_PuPd,GPIO_Label,GPIO_ModeDefaultEXTI
PB14.GPIO_Label=SW_UP
PB14.GPIO_ModeDefaultEXTI=GPIO_MODE_IT_FALLING
PB14.GPIO_PuPd=GPIO_PULLUP
PB14.Signal=GPXTI14
PB15.GPIOParameters=GPIO_PuPd,GPIO_Label,GPIO_ModeDefaultEXTI
PB15.GPIO_Label=SW_MENU
PB15.GPIO_ModeDefaultEXTI=GPIO_MODE_IT_FALLING
PB15.GPIO_PuPd=GPIO_PULLUP
PB15.Signal=GPXTI15
PB2.GPIOParameters=GPIO_Label
PB2.GPIO_Label=LIGHT_EN
PB2.Mode=WaveformGeneration
PB2.Signal=LPTIM1_OUT
PB3.GPIOParameters=GPIO_Label
PB3.GPIO_Label=LCD_SCK
PB3.Mode=TX_Only_Simplex_Unidirect_Master
PB3.Signal=SPI1_SCK
PB5.GPIOParameters=GPIO_Label
PB5.GPIO_Label=LCD_MOSI
PB5.Mode=TX_Only_Simplex_Unidirect_Master
PB5.Signal=SPI1_MOSI
PB6.GPIOParameters=GPIO_PuPd,GPIO_Label,GPIO_ModeDefaultEXTI
PB6.GPIO_Label=SW_DOWN
PB6.GPIO_ModeDefaultEXTI=GPIO_MODE_IT_FALLING
PB6.GPIO_PuPd=GPIO_PULLUP
PB6.Signal=GPXTI6
PB7.GPIOParameters=GPIO_Label
PB7.GPIO_Label=IMU_SDA
PB7.Mode=I2C
PB7.Signal=I2C1_SDA
PB8.GPIOParameters=GPIO_Label
PB8.GPIO_Label=IMU_INT1
PB8.Signal=GPIO_Input
PB9.GPIOParameters=GPIO_Label
PB9.GPIO_Label=SW_RESET
PB9.Signal=GPIO_Input
PC0.GPIOParameters=GPIO_Label
PC0.GPIO_Label=IMU_INT2
PC0.Signal=GPIO_Input
PC1.GPIOParameters=GPIO_Label
PC1.GPIO_Label=FG_SDA
PC1.Mode=I2C
PC1.Signal=I2C3_SDA
PC13.GPIOParameters=GPIO_PuPd,GPIO_Label,GPIO_ModeDefaultOutputPP
PC13.GPIO_Label=LCD_REFRESH
PC13.GPIO_ModeDefaultOutputPP=GPIO_MODE_OUTPUT_PP
PC13.GPIO_PuPd=GPIO_PULLUP
PC13.Signal=GPIO_Output
PC14-OSC32_IN.Mode=LSE-External-Oscillator
PC14-OSC32_IN.Signal=RCC_OSC32_IN
PC15-OSC32_OUT.Mode=LSE-External-Oscillator
PC15-OSC32_OUT.Signal=RCC_OSC32_OUT
PC2.GPIOParameters=GPIO_Label
PC2.GPIO_Label=FG_INT
PC2.Signal=GPIO_Input
PH3-BOOT0.GPIOParameters=GPIO_PuPd,GPIO_Label,GPIO_ModeDefaultEXTI
PH3-BOOT0.GPIO_Label=SW_LIGHT
PH3-BOOT0.GPIO_ModeDefaultEXTI=GPIO_MODE_IT_RISING_FALLING
PH3-BOOT0.GPIO_PuPd=GPIO_NOPULL
PH3-BOOT0.Signal=GPXTI3
RCC.HSE_VALUE=32000000
RCC.SYSCLKFreq_VALUE=64000000
RCC.SYSCLKSource=RCC_SYSCLKSOURCE_PLLCLK
board=custom

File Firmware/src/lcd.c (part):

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#define LCD_HOST  SPI2_HOST

#define LCD_PIXEL_CLOCK_HZ (60 * 1000 * 1000)// (20 * 1000 * 1000)
#define LCD_SCLK_PIN 2
#define LCD_MOSI_PIN 3
#define LCD_MISO_PIN 0
#define LCD_DC_PIN 7
#define LCD_RST_PIN 6
#define LCD_CS_PIN 10
#define LCD_BL_PIN 5

#define LCD_H_RES 240
#define LCD_V_RES 240
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  static lv_disp_drv_t disp_drv;      // contains callback functions

  ESP_LOGI(_TAG, "initialize backlight pwm");
  gpio_sleep_sel_dis(LCD_BL_PIN);
  // Prepare and then apply the LEDC PWM timer configuration
  ledc_timer_config_t ledc_timer = {
      .speed_mode       = LEDC_MODE,
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      .channel        = LEDC_CHANNEL,
      .timer_sel      = LEDC_TIMER,
      .intr_type      = LEDC_INTR_DISABLE,
      .gpio_num       = LCD_BL_PIN,
      .duty           = 0, // Set duty to 0%
      .hpoint         = 0
  };
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
  ESP_LOGI(_TAG, "initialize spi bus");
  spi_bus_config_t buscfg = {
      .sclk_io_num = LCD_SCLK_PIN,
      .mosi_io_num = LCD_MOSI_PIN,
      .miso_io_num = LCD_MISO_PIN,
      .quadwp_io_num = -1,
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  ESP_LOGI(_TAG, "install panel io");
  esp_lcd_panel_io_handle_t io_handle = NULL;
  esp_lcd_panel_io_spi_config_t io_config = {
      .dc_gpio_num = LCD_DC_PIN,
      .cs_gpio_num = LCD_CS_PIN,
      .pclk_hz = LCD_PIXEL_CLOCK_HZ,
      .lcd_cmd_bits = LCD_CMD_BITS,
      .lcd_param_bits = LCD_PARAM_BITS,
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
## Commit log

2023-12-17 Notifications rewrite
2023-12-18 Start hardware
2023-12-19 st7789 working
2023-12-19 Separate LCD code and modem sleep actually works
2023-12-21 Animation! And power saving tweaks
    Idle current is down to ~40ma at 25% brightness
2023-12-24 Schematic progress
2023-12-24 Tidy up and notification text scrolling attempt
2023-12-29 Many things
    40ma at 25% brightness connected
    30ma at 25% brightness disconnected
2024-01-11 Hardware done and ordered 🤞
2024-02-05 Start V2
2024-02-08 Trying to get toolchain working
2024-02-09 Blinky working
2024-02-09 Maybe I'll stick with ESP32-C3, nrf52 is proving a pain to work with
2024-02-14 Back to basics, modem sleep works in this minimal example
2024-02-14 Found a decent e-ink driver
2024-02-14 E-ink and BLE won't work at the same time :(
2024-02-18 Just gonna use arduino for nrf52 version
2024-03-09 E-ink and BLE working at same time
2024-03-10 Start seperating eink driver into new file
2024-03-10 Cleanup e-ink code
2024-03-10 Start reintroducing gadgetbridge code
2024-03-10 Gadgetbridge working again
2024-03-10 Display latest notification
2024-03-11 Just a few of very minor changes
2024-03-11 Update V1 schematic to e-ink
2024-03-11 Rename V1 and V2 to ESP32 and NRF52
2024-03-31 Progress on NRF52 version hardware
2024-04-01 Correct e-ink driver components
2024-04-03 NRF52 hardware as ordered
2024-04-03 Fix timezones on ESP32 version
2024-04-19 Start circuitpython version of software
2024-04-19 Move gadgetbridge stuff to own file
2024-04-19 Start on some new watchfaces
2024-04-20 Add missing files and start on button input
2024-04-21 Start menu system
2024-07-22 Miscellaneous small software improvements
2024-08-02 Start STM32WB version schematic
2024-08-12 Schematic progress and start PCB
2024-08-17 Ordered
2024-08-24 Start STM32WB firmware
2024-08-25 Basic watch functionality
2024-08-27 Enable HSE and LSE
2024-08-27 Set all unused pins to analog to save power
2024-08-29 RTC calibration and button debouncing
2024-10-06 Fix day of week crashing on Mondays and set terminate voltage on fuel gauge
